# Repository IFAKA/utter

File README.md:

# Utter

**Live demo: https://utter-nine.vercel.app** · Goal: an open-source, non-invasive voice for people who cannot speak (for example ALS), measured in words per minute and word error rate on mimed speech.

Covert text input: silently articulate (lips closed, no sound) and text appears in any app.
Surface EMG (chin/throat/behind ear) -> Utter (2x ADS1298 = 16 ch + ESP32-S3) -> ~8 silent tokens -> local LLM suggestions -> earbud feedback -> typed text.

**Not a medical device.** Battery-powered operation only; the firmware refuses to record while USB is connected.

- docs/PLAN.md: stages and pass/fail gates
- docs/USAGE.md: setup and the user's 6 steps
- docs/HARDWARE.md, docs/ORDER.md: board design and order card
- Layout: hardware/ (generated KiCad board, `hardware/gen/build.sh`), firmware/ (PlatformIO), ml/ (`utter` host tools), app/ (Mac menu-bar app)

## Third-party data
- app/Sources/TypingCore/Resources/words_{en,es}.txt are derived from wordfreq (https://github.com/rspeer/wordfreq) word lists, CC-BY-SA 4.0. The derived lists keep that license.
- The Gaddy & Klein silent-speech EMG dataset (https://zenodo.org/records/4064409), CC-BY-4.0, is downloaded locally and not redistributed.

## Status
Early research. The board is designed (DRC/ERC clean) but not built or ordered. Nothing here is validated on people yet; see docs/PLAN.md for the pass/fail gates.

## License
No license chosen yet. Word lists keep CC-BY-SA 4.0 (see above).

---

## Support

If this project is useful to you, you can support my work:

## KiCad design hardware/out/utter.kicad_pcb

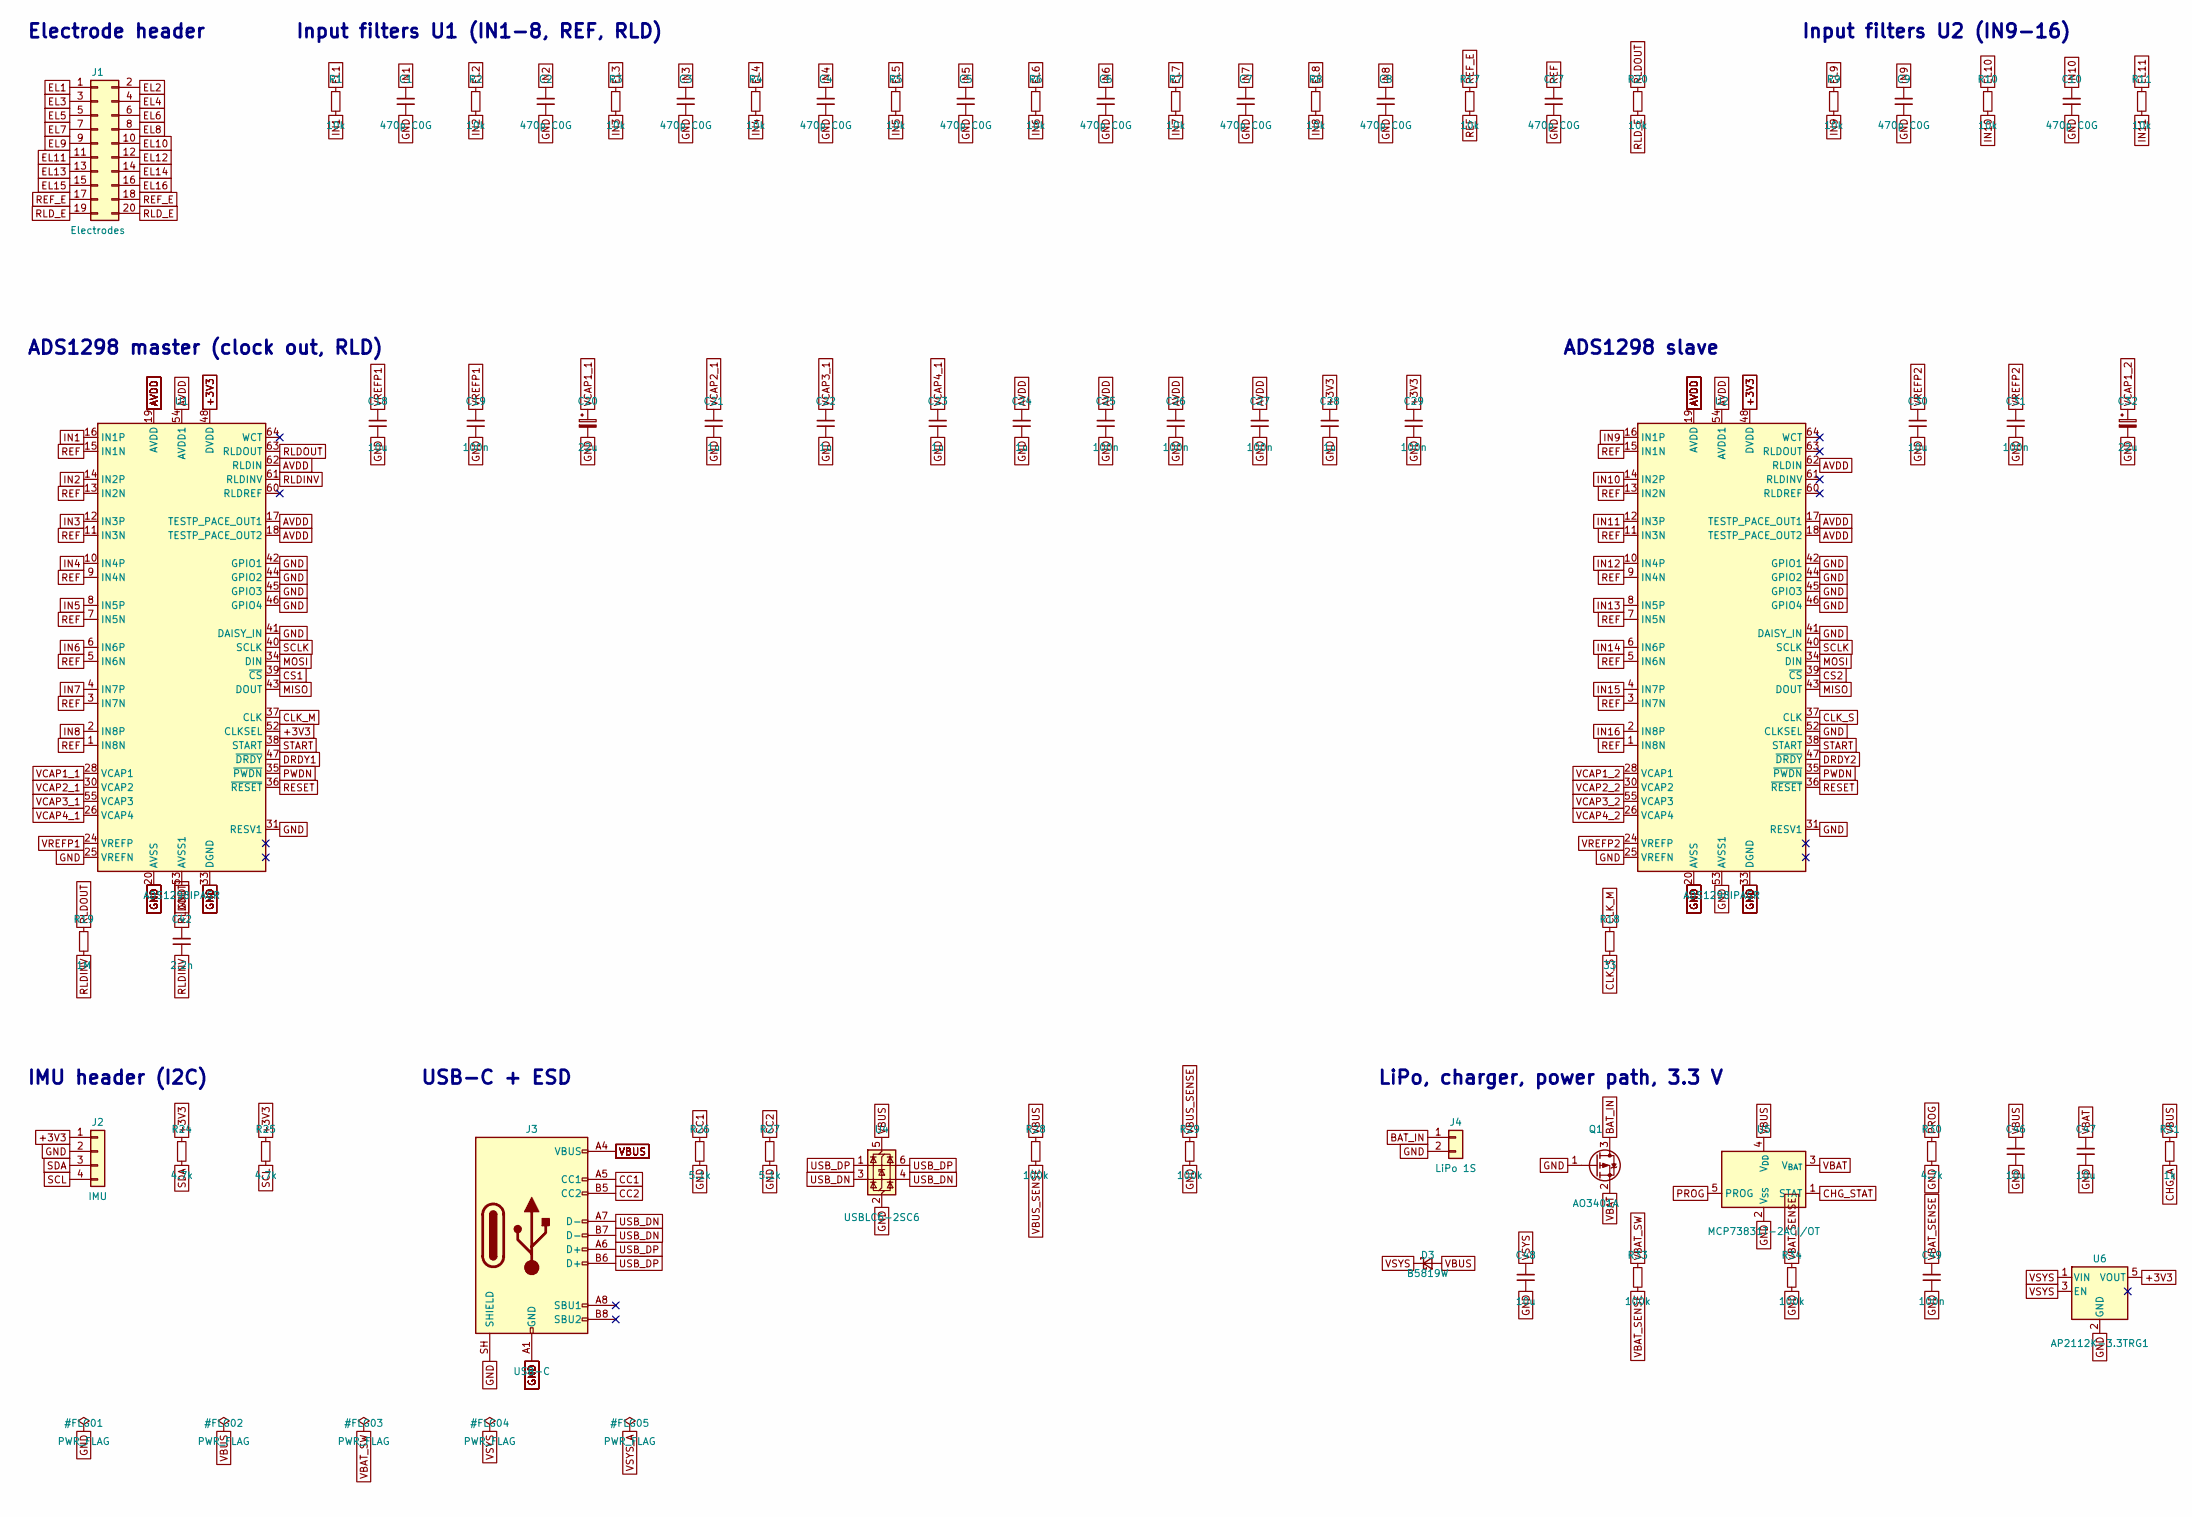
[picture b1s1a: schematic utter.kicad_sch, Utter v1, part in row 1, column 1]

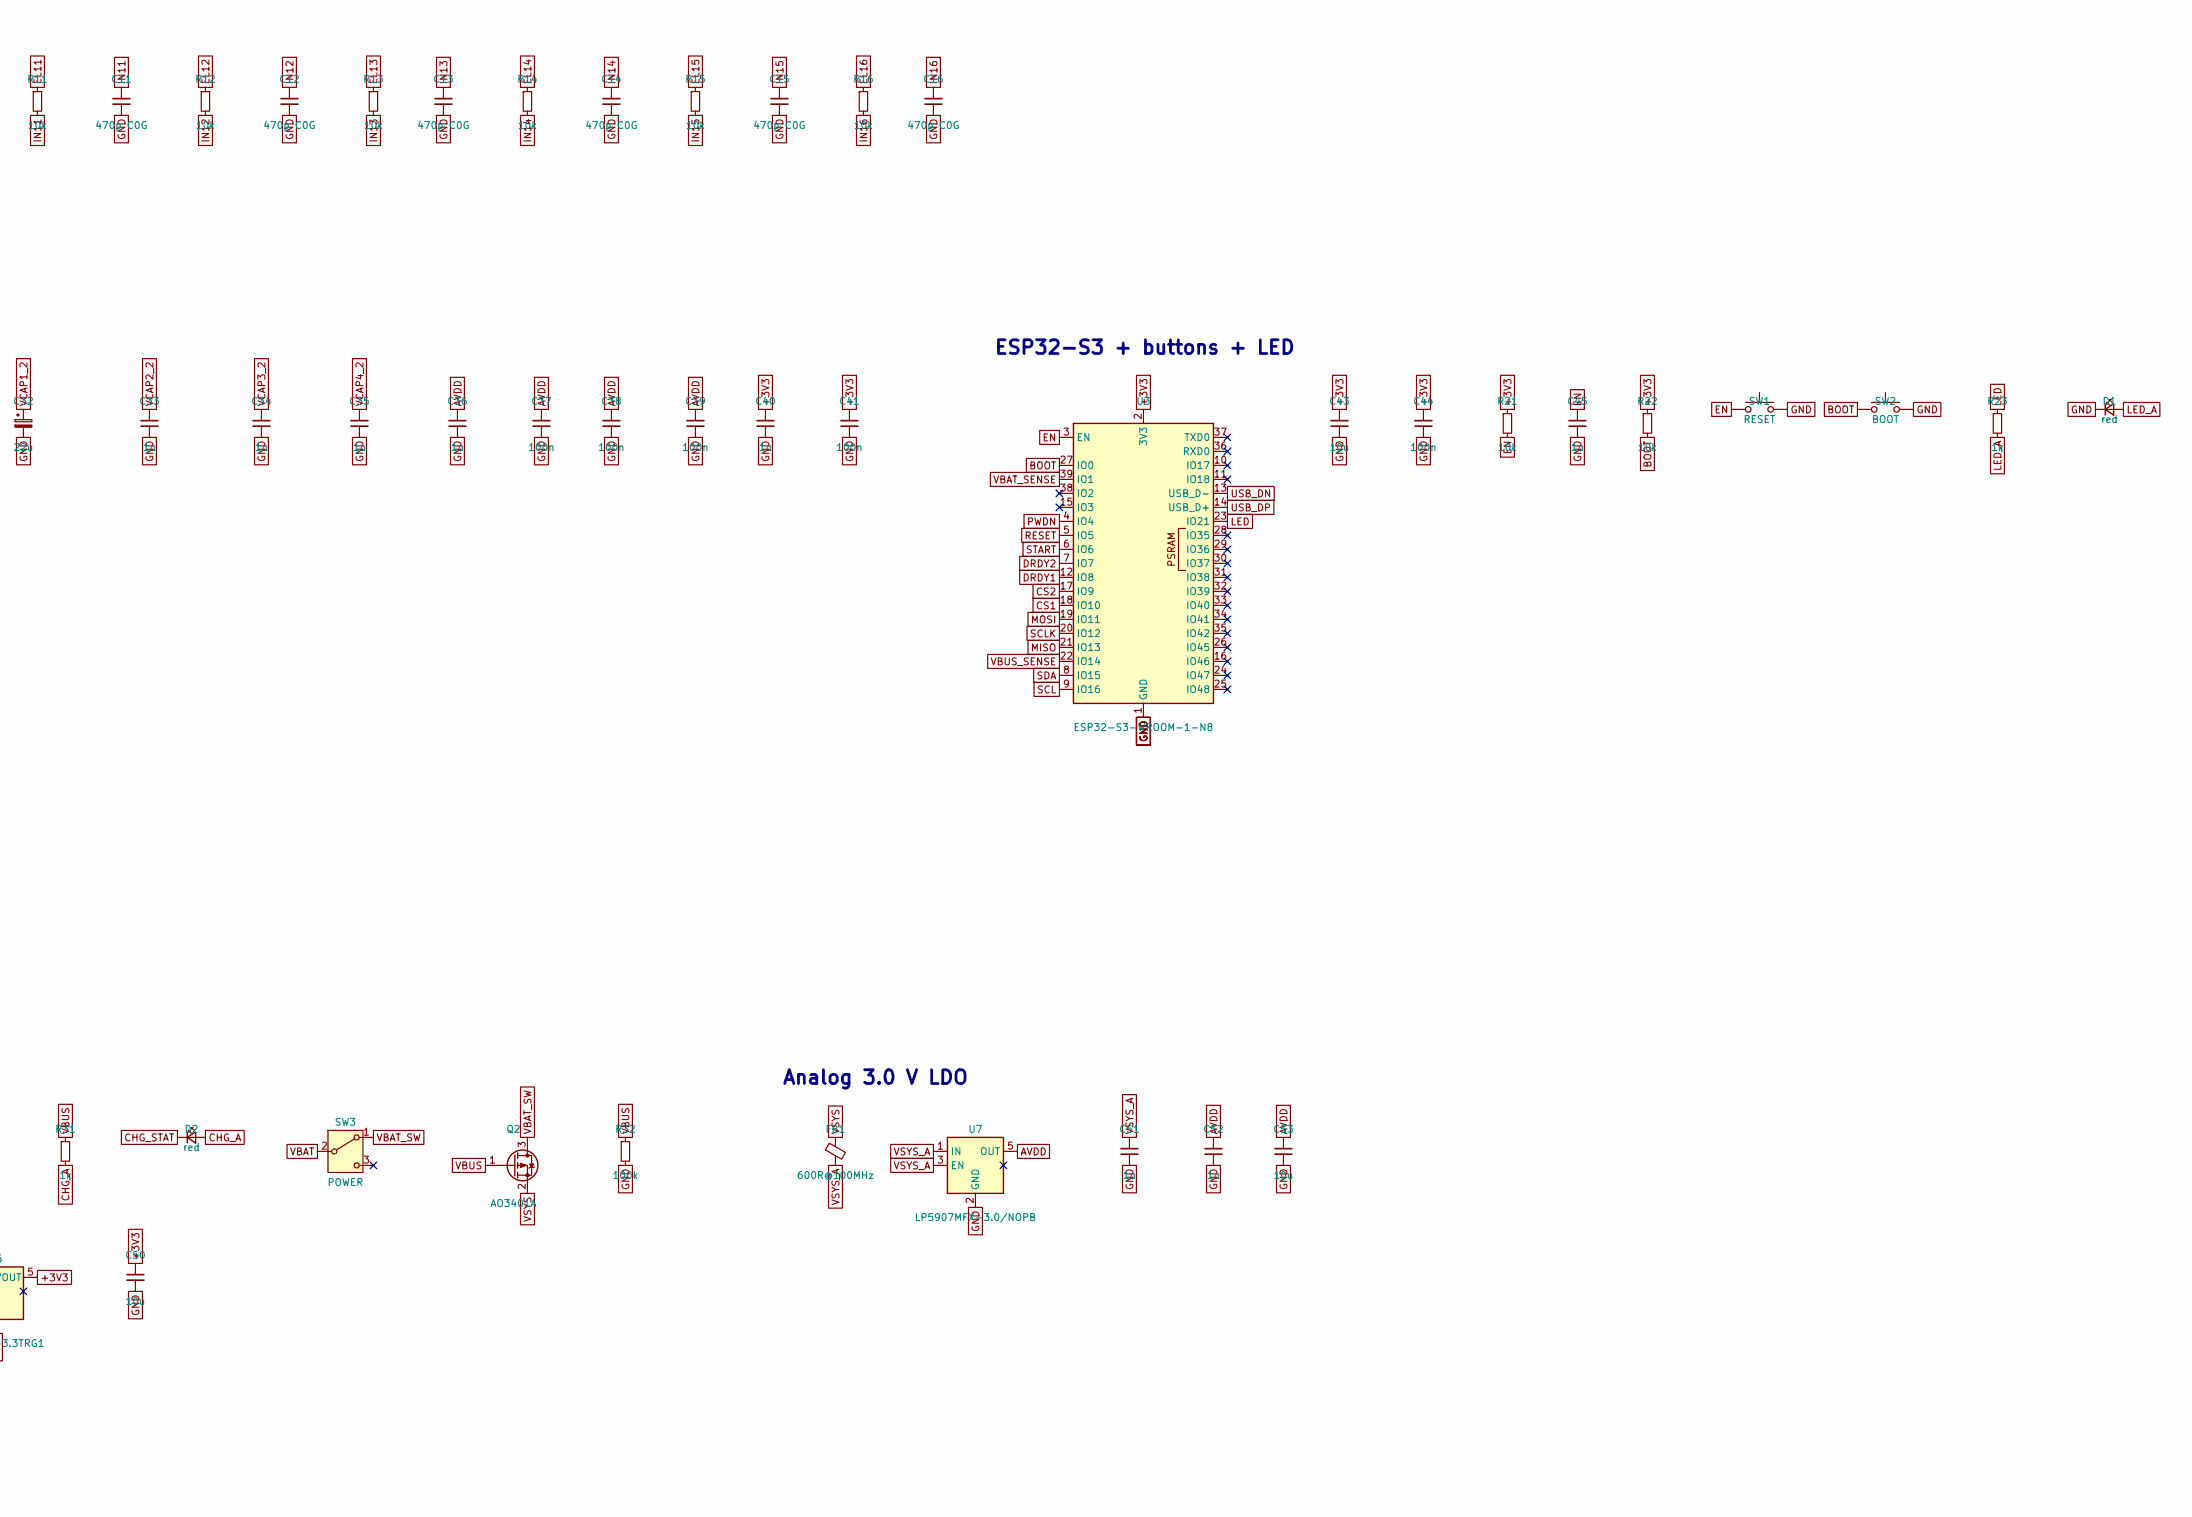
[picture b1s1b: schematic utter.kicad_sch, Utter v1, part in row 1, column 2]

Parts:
C1, C2, C3, C4, C5, C6, C7, C8, C9, C10, C11, C12, C13, C14, C15, C16, C17: 470p C0G; C_0402_1005Metric; LCSC C75274
C18, C30, C43, C46, C47, C48, C50, C53: 10u; C_0603_1608Metric; LCSC C19702
C19, C25, C26, C27, C29, C31, C37, C38, C39, C41, C44, C49: 100n; C_0402_1005Metric; LCSC C1525
C20, C32: 22u; CP_EIA-3216-18_Kemet-A; LCSC C7183
C21, C22, C23, C24, C28, C33, C34, C35, C36, C40, C45, C51, C52: 1u; C_0603_1608Metric; LCSC C15849
C42: 2.2n; C_0603_1608Metric; LCSC C1604
D1, D2: red; LED_0603_1608Metric; LCSC C2286
D3: B5819W; D_SOD-123; LCSC C8598
FB1: 600R@100MHz; L_0603_1608Metric; LCSC C1002
J1: Electrodes; PinHeader_2x10_P2.54mm_Vertical_SMD; LCSC C42372532
J2: IMU; PinHeader_1x04_P2.54mm_Vertical_SMD_Pin1Left; LCSC C46061677
J3: USB-C; USB_C_Receptacle_HRO_TYPE-C-31-M-12; LCSC C165948
J4: LiPo 1S; JST_PH_S2B-PH-SM4-TB_1x02-1MP_P2.00mm_Horizontal; LCSC C295747
Q1, Q2: AO3401A; SOT-23; LCSC C15127
R1, R2, R3, R4, R5, R6, R7, R8, R9, R10, R11, R12, R13, R14, R15, R16, R17, R20, R21, R22: 10k; R_0402_1005Metric; LCSC C25744
R18: 33; R_0402_1005Metric; LCSC C25105
R19: 1M; R_0402_1005Metric; LCSC C26083
R23, R31: 1k; R_0402_1005Metric; LCSC C11702
R24, R25, R30: 4.7k; R_0402_1005Metric; LCSC C25900
R26, R27: 5.1k; R_0402_1005Metric; LCSC C25905
R28, R29, R32, R33, R34: 100k; R_0402_1005Metric; LCSC C25741
SW1: RESET; SW_Push_1P1T_XKB_TS-1187A; LCSC C318884
SW2: BOOT; SW_Push_1P1T_XKB_TS-1187A; LCSC C318884
SW3: POWER; SW_SPDT_Shouhan_MSK12C02; LCSC C431540
U1, U2: ADS1298IPAGR; TQFP-64_10x10mm_P0.5mm; LCSC C527440
U3: ESP32-S3-WROOM-1-N8; ESP32-S3-WROOM-1; LCSC C2913198
U4: USBLC6-2SC6; SOT-23-6; LCSC C7519
U5: MCP73831T-2ACI/OT; SOT-23-5; LCSC C424093
U6: AP2112K-3.3TRG1; SOT-23-5; LCSC C51118
U7: LP5907MFX-3.0/NOPB; SOT-23-5; LCSC C475492

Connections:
+3V3: C28.1, C29.1, C40.1, C41.1, C43.1, C44.1, C50.1, J2.1, R21.1, R22.1, R24.1, R25.1, U1.48 (DVDD), U1.50 (DVDD), U1.52 (CLKSEL), U2.48 (DVDD), U2.50 (DVDD), U3.2 (3V3), U6.5 (VOUT)
AVDD: C24.1, C25.1, C26.1, C27.1, C36.1, C37.1, C38.1, C39.1, C52.1, C53.1, U1.17 (TESTP_PACE_OUT1), U1.18 (TESTP_PACE_OUT2), U1.19 (AVDD), U1.21 (AVDD), U1.22 (AVDD), U1.54 (AVDD1), U1.56 (AVDD), U1.59 (AVDD), U1.62 (RLDIN), U2.17 (TESTP_PACE_OUT1), U2.18 (TESTP_PACE_OUT2), U2.19 (AVDD), U2.21 (AVDD), U2.22 (AVDD), U2.54 (AVDD1), U2.56 (AVDD), U2.59 (AVDD), U2.62 (RLDIN), U7.5 (OUT)
BAT_IN: J4.1, Q1.3 (D)
BOOT: R22.2, SW2.1, U3.27 (IO0)
CC1: J3.A5 (CC1), R26.1
CC2: J3.B5 (CC2), R27.1
CHG_A: D2.2 (A), R31.2
CHG_STAT: D2.1 (K), U5.1 (STAT)
CLK_M: R18.1, U1.37 (CLK)
CLK_S: R18.2, U2.37 (CLK)
CS1: U1.39 (~CS), U3.18 (IO10)
CS2: U2.39 (~CS), U3.17 (IO9)
DRDY1: U1.47 (~DRDY), U3.12 (IO8)
DRDY2: U2.47 (~DRDY), U3.7 (IO7)
EL1: J1.1, R1.1
EL2: J1.2, R2.1
EL3: J1.3, R3.1
EL4: J1.4, R4.1
EL5: J1.5, R5.1
EL6: J1.6, R6.1
EL7: J1.7, R7.1
EL8: J1.8, R8.1
EL9: J1.9, R9.1
EL10: J1.10, R10.1
EL11: J1.11, R11.1
EL12: J1.12, R12.1
EL13: J1.13, R13.1
EL14: J1.14, R14.1
EL15: J1.15, R15.1
EL16: J1.16, R16.1
EN: C45.1, R21.2, SW1.1, U3.3 (EN)
GND: C1.2, C2.2, C3.2, C4.2, C5.2, C6.2, C7.2, C8.2, C9.2, C10.2, C11.2, C12.2, C13.2, C14.2, C15.2, C16.2, C17.2, C18.2, C19.2, C20.2, C21.2, C22.2, C23.2, C24.2, C25.2, C26.2, C27.2, C28.2, C29.2, C30.2, C31.2, C32.2, C33.2, C34.2, C35.2, C36.2, C37.2, C38.2, C39.2, C40.2, C41.2, C43.2, C44.2, C45.2, C46.2, C47.2, C48.2, C49.2, C50.2, C51.2, C52.2, C53.2, D1.1 (K), J2.2, J3.A1 (GND), J3.A12 (GND), J3.B1 (GND), J3.B12 (GND), J3.SH (SHIELD), J4.2, J4.MP, Q1.1 (G), R26.2, R27.2, R29.2, R30.2, R32.2, R34.2, SW1.2, SW2.2, SW3.SH, U1.20 (AVSS), U1.23 (AVSS), U1.25 (VREFN), U1.31 (RESV1), U1.32 (AVSS), U1.33 (DGND), U1.41 (DAISY_IN), U1.42 (GPIO1), U1.44 (GPIO2), U1.45 (GPIO3), U1.46 (GPIO4), U1.49 (DGND), U1.51 (DGND), U1.53 (AVSS1), U1.57 (AVSS), U1.58 (AVSS), U2.20 (AVSS), U2.23 (AVSS), U2.25 (VREFN), U2.31 (RESV1), U2.32 (AVSS), U2.33 (DGND), U2.41 (DAISY_IN), U2.42 (GPIO1), U2.44 (GPIO2), U2.45 (GPIO3), U2.46 (GPIO4), U2.49 (DGND), U2.51 (DGND), U2.52 (CLKSEL), U2.53 (AVSS1), U2.57 (AVSS), U2.58 (AVSS), U3.1 (GND), U3.40 (GND), U3.41 (GND), U4.2 (GND), U5.2 (V_{SS}), U6.2 (GND), U7.2 (GND)
IN1: C1.1, R1.2, U1.16 (IN1P)
IN2: C2.1, R2.2, U1.14 (IN2P)
IN3: C3.1, R3.2, U1.12 (IN3P)
IN4: C4.1, R4.2, U1.10 (IN4P)
IN5: C5.1, R5.2, U1.8 (IN5P)
IN6: C6.1, R6.2, U1.6 (IN6P)
IN7: C7.1, R7.2, U1.4 (IN7P)
IN8: C8.1, R8.2, U1.2 (IN8P)
IN9: C9.1, R9.2, U2.16 (IN1P)
IN10: C10.1, R10.2, U2.14 (IN2P)
IN11: C11.1, R11.2, U2.12 (IN3P)
IN12: C12.1, R12.2, U2.10 (IN4P)
IN13: C13.1, R13.2, U2.8 (IN5P)
IN14: C14.1, R14.2, U2.6 (IN6P)
IN15: C15.1, R15.2, U2.4 (IN7P)
IN16: C16.1, R16.2, U2.2 (IN8P)
LED: R23.1, U3.23 (IO21)
LED_A: D1.2 (A), R23.2
MISO: U1.43 (DOUT), U2.43 (DOUT), U3.21 (IO13)
MOSI: U1.34 (DIN), U2.34 (DIN), U3.19 (IO11)
NC_LDO1: U6.4 (NC)
NC_LDO2: U7.4 (NC)
NC_SW: SW3.3 (C)
PROG: R30.1, U5.5 (PROG)
PWDN: U1.35 (~PWDN), U2.35 (~PWDN), U3.4 (IO4)
REF: C17.1, R17.2, U1.1 (IN8N), U1.3 (IN7N), U1.5 (IN6N), U1.7 (IN5N), U1.9 (IN4N), U1.11 (IN3N), U1.13 (IN2N), U1.15 (IN1N), U2.1 (IN8N), U2.3 (IN7N), U2.5 (IN6N), U2.7 (IN5N), U2.9 (IN4N), U2.11 (IN3N), U2.13 (IN2N), U2.15 (IN1N)
REF_E: J1.17, J1.18, R17.1
RESET: U1.36 (~RESET), U2.36 (~RESET), U3.5 (IO5)
RLDINV: C42.2, R19.2, U1.61 (RLDINV)
RLDOUT: C42.1, R19.1, R20.1, U1.63 (RLDOUT)
RLD_E: J1.19, J1.20, R20.2
SCL: J2.4, R25.2, U3.9 (IO16)
SCLK: U1.40 (SCLK), U2.40 (SCLK), U3.20 (IO12)
SDA: J2.3, R24.2, U3.8 (IO15)
START: U1.38 (START), U2.38 (START), U3.6 (IO6)
USB_DN: J3.A7 (D-), J3.B7 (D-), U3.13 (USB_D-), U4.3 (I/O2), U4.4 (I/O2)
USB_DP: J3.A6 (D+), J3.B6 (D+), U3.14 (USB_D+), U4.1 (I/O1), U4.6 (I/O1)
VBAT: C47.1, Q1.2 (S), SW3.2 (B), U5.3 (V_{BAT})
VBAT_SENSE: C49.1, R33.2, R34.1, U3.39 (IO1)
VBAT_SW: Q2.3 (D), R33.1, SW3.1 (A)
VBUS: C46.1, D3.2 (A), J3.A4 (VBUS), J3.A9 (VBUS), J3.B4 (VBUS), J3.B9 (VBUS), Q2.1 (G), R28.1, R31.1, R32.1, U4.5 (VBUS), U5.4 (V_{DD})
VBUS_SENSE: R28.2, R29.1, U3.22 (IO14)
VCAP1_1: C20.1, U1.28 (VCAP1)
VCAP1_2: C32.1, U2.28 (VCAP1)
VCAP2_1: C21.1, U1.30 (VCAP2)
VCAP2_2: C33.1, U2.30 (VCAP2)
VCAP3_1: C22.1, U1.55 (VCAP3)
VCAP3_2: C34.1, U2.55 (VCAP3)
VCAP4_1: C23.1, U1.26 (VCAP4)
VCAP4_2: C35.1, U2.26 (VCAP4)
VREFP1: C18.1, C19.1, U1.24 (VREFP)
VREFP2: C30.1, C31.1, U2.24 (VREFP)
VSYS: C48.1, D3.1 (K), FB1.1, Q2.2 (S), U6.1 (VIN), U6.3 (EN)
VSYS_A: C51.1, FB1.2, U7.1 (IN), U7.3 (EN)

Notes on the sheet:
Electrode header
Input filters U1 (IN1-8, REF, RLD)
Input filters U2 (IN9-16)
ADS1298 master (clock out, RLD)
ADS1298 slave
ESP32-S3 + buttons + LED
IMU header (I2C)
USB-C + ESD
LiPo, charger, power path, 3.3 V
Analog 3.0 V LDO

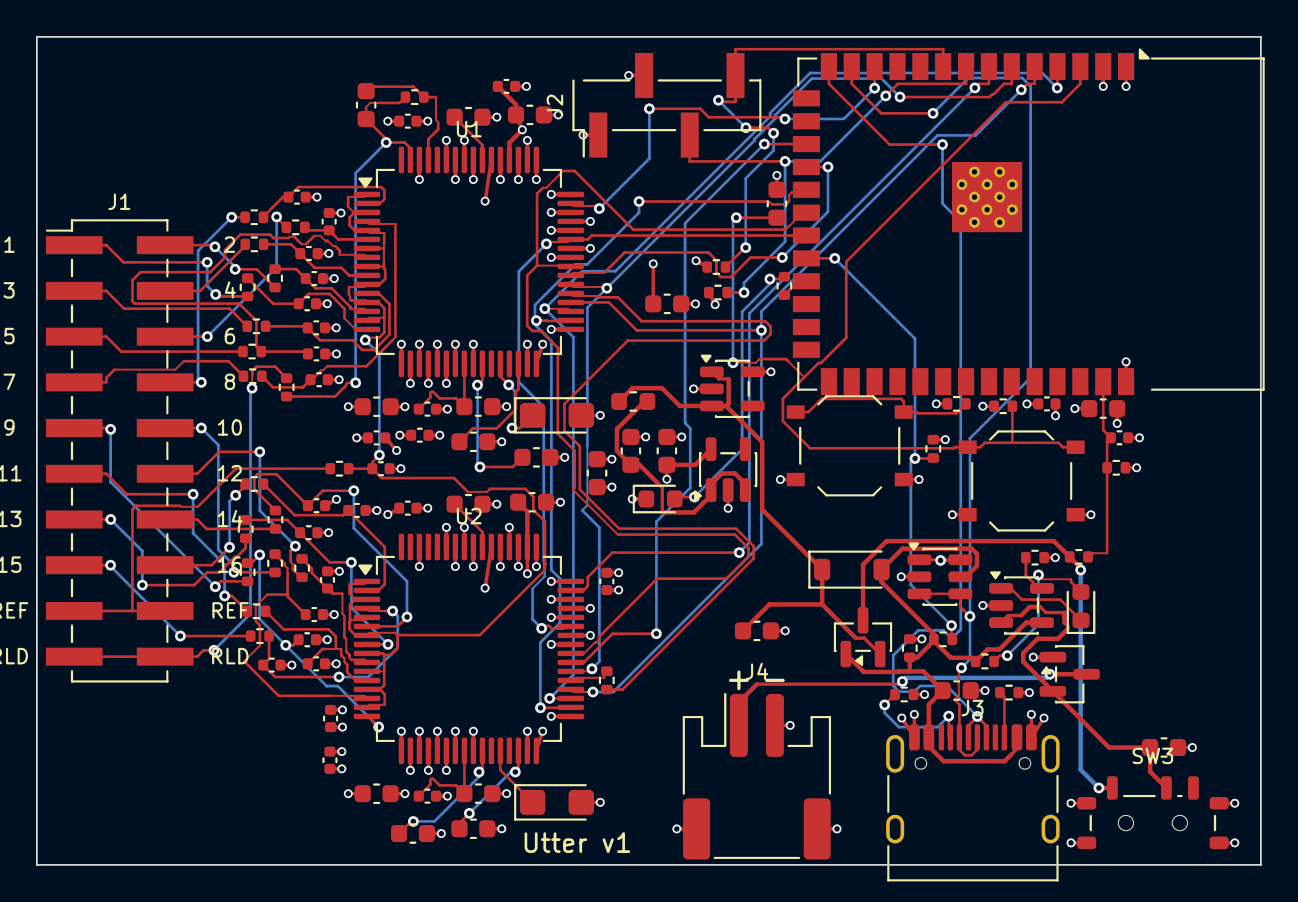
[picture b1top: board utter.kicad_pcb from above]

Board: 4 copper layers, 68.0 x 46.0 mm, 107 parts (0 on the bottom side), 83 nets.

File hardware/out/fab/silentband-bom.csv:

Comment,Designator,Footprint,LCSC Part #,Quantity
470p C0G,"C1,C2,C3,C4,C5,C6,C7,C8,C9,C10,C11,C12,C13,C14,C15,C16,C17",C_0402_1005Metric,C75274,17
10u,"C18,C30,C43,C46,C47,C48,C50,C53",C_0603_1608Metric,C19702,8
100n,"C19,C25,C26,C27,C29,C31,C37,C38,C39,C41,C44,C49",C_0402_1005Metric,C1525,12
22u,"C20,C32",CP_EIA-3216-18_Kemet-A,C7183,2
1u,"C21,C22,C23,C24,C28,C33,C34,C35,C36,C40,C45,C51,C52",C_0603_1608Metric,C15849,13
2.2n,C42,C_0603_1608Metric,C1604,1
red,"D1,D2",LED_0603_1608Metric,C2286,2
B5819W,D3,D_SOD-123,C8598,1
600R@100MHz,FB1,L_0603_1608Metric,C1002,1
Electrodes,J1,PinHeader_2x10_P2.54mm_Vertical_SMD,C42372532,1
IMU,J2,PinHeader_1x04_P2.54mm_Vertical_SMD_Pin1Left,C46061677,1
USB-C,J3,USB_C_Receptacle_HRO_TYPE-C-31-M-12,C165948,1
LiPo 1S,J4,JST_PH_S2B-PH-SM4-TB_1x02-1MP_P2.00mm_Horizontal,C295747,1
AO3401A,"Q1,Q2",SOT-23,C15127,2
10k,"R1,R2,R3,R4,R5,R6,R7,R8,R9,R10,R11,R12,R13,R14,R15,R16,R17,R20,R21,R22",R_0402_1005Metric,C25744,20
33,R18,R_0402_1005Metric,C25105,1
1M,R19,R_0402_1005Metric,C26083,1
1k,"R23,R31",R_0402_1005Metric,C11702,2
4.7k,"R24,R25,R30",R_0402_1005Metric,C25900,3
5.1k,"R26,R27",R_0402_1005Metric,C25905,2
100k,"R28,R29,R32,R33,R34",R_0402_1005Metric,C25741,5
RESET,SW1,SW_Push_1P1T_XKB_TS-1187A,C318884,1
BOOT,SW2,SW_Push_1P1T_XKB_TS-1187A,C318884,1
POWER,SW3,SW_SPDT_Shouhan_MSK12C02,C431540,1
ADS1298IPAGR,"U1,U2",TQFP-64_10x10mm_P0.5mm,C527440,2
ESP32-S3-WROOM-1-N8,U3,ESP32-S3-WROOM-1,C2913198,1
USBLC6-2SC6,U4,SOT-23-6,C7519,1
MCP73831T-2ACI/OT,U5,SOT-23-5,C424093,1
AP2112K-3.3TRG1,U6,SOT-23-5,C51118,1
LP5907MFX-3.0/NOPB,U7,SOT-23-5,C475492,1

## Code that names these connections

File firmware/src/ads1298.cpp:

#include "ads1298.h"
#include "pins.h"
#include <driver/gpio.h>

namespace ads {
static SPIClass spi(FSPI);
static const SPISettings cfg(8000000, MSBFIRST, SPI_MODE1);
static const int cs[NCHIP] = {PIN_CS1, PIN_CS2};
// fCLK = 2.048 MHz: multi-byte commands need 4 tCLK (~2 us) between bytes.
static inline void tdecode() { delayMicroseconds(3); }

enum Op : uint8_t { WAKEUP = 0x02, RESET = 0x06, RDATAC = 0x10, SDATAC = 0x11, RREG = 0x20, WREG = 0x40 };

static void op(int chip, uint8_t c) {
  spi.beginTransaction(cfg);
  digitalWrite(cs[chip], LOW);
  spi.transfer(c);
  tdecode();
  digitalWrite(cs[chip], HIGH);
  spi.endTransaction();
}

uint8_t readReg(int chip, uint8_t reg) {
  spi.beginTransaction(cfg);
  digitalWrite(cs[chip], LOW);
  spi.transfer(RREG | reg); tdecode();
  spi.transfer(0); tdecode();
  uint8_t v = spi.transfer(0); tdecode();
  digitalWrite(cs[chip], HIGH);
  spi.endTransaction();
  return v;
}

void writeReg(int chip, uint8_t reg, uint8_t val) {
  spi.beginTransaction(cfg);
  digitalWrite(cs[chip], LOW);
  spi.transfer(WREG | reg); tdecode();
  spi.transfer(0); tdecode();
  spi.transfer(val); tdecode();
  digitalWrite(cs[chip], HIGH);
  spi.endTransaction();
}

// HR-mode DR codes; CONFIG1 = HR | DAISY_EN (multiple readback) | CLK_EN (master only) | DR.
static int drCode(int fs) {
  switch (fs) {
    case 500: return 6; case 1000: return 5; case 2000: return 4; case 4000: return 3;
    default: return -1;
  }
}
static int gainCode(int g) {
  switch (g) {
    case 6: return 0; case 1: return 1; case 2: return 2; case 3: return 3;
    case 4: return 4; case 8: return 5; case 12: return 6; default: return -1;
  }
}

void begin() {
  for (int c : cs) { pinMode(c, OUTPUT); digitalWrite(c, HIGH); }
  pinMode(PIN_START, OUTPUT); digitalWrite(PIN_START, LOW);
  pinMode(PIN_RESET, OUTPUT); digitalWrite(PIN_RESET, HIGH);
  pinMode(PIN_PWDN, OUTPUT); digitalWrite(PIN_PWDN, HIGH);
  pinMode(PIN_DRDY1, INPUT_PULLUP);
  pinMode(PIN_DRDY2, INPUT_PULLUP);
  spi.begin(PIN_SCLK, PIN_MISO, PIN_MOSI, -1);
  // weakest drive = slowest edges: SPI/control lines partly run on B.Cu over the analog half
  for (int p : {PIN_SCLK, PIN_MOSI, PIN_CS1, PIN_CS2, PIN_START, PIN_RESET, PIN_PWDN})
    gpio_set_drive_capability((gpio_num_t)p, GPIO_DRIVE_CAP_0);
  delay(200);                                   // power-on reset: 2^18 tCLK = 128 ms
  digitalWrite(PIN_RESET, LOW); delayMicroseconds(10); digitalWrite(PIN_RESET, HIGH);
  delayMicroseconds(20);                        // 18 tCLK
  op(0, SDATAC);
  writeReg(0, CONFIG1, 0xE4);                   // master: CLK_EN so the slave gets a clock
  delay(150);                                   // slave tPOR (128 ms) starts only once CLK is valid
  op(1, RESET);                                 // the slave now has a clock: reset it properly
  delayMicroseconds(20);
  op(1, SDATAC);
  for (int c = 0; c < NCHIP; c++) writeReg(c, CONFIG3, 0xC0);  // internal reference on
  delay(150);                                   // reference settling
}

bool configure(int fs, int gain, Mode mode, bool leadoff) {
  int dr = drCode(fs), g = gainCode(gain);
  if (dr < 0 || g < 0) return false;
  for (int c = 0; c < NCHIP; c++) {
    bool master = c == 0;
    writeReg(c, CONFIG1, 0x80 | 0x40 | (master ? 0x20 : 0) | dr);
    writeReg(c, CONFIG2, mode == TEST ? 0x10 : 0x00);         // internal test: 1 mV, fCLK/2^21
    // Refbuf on, RLDREF internal; only the master drives the right-leg (RLD) electrode.
    writeReg(c, CONFIG3, master ? 0xCC : 0xC8);
    writeReg(c, LOFF, 0x00);                                  // DC lead-off, 6 nA, 95% threshold
    for (int ch = 0; ch < 8; ch++) writeReg(c, CH1SET + ch, (g << 4) | mode);
    uint8_t rld = (master && mode == NORMAL) ? 0xFF : 0x00;
    writeReg(c, RLD_SENSP, rld);
    writeReg(c, RLD_SENSN, rld);
    uint8_t lo = (leadoff && mode == NORMAL) ? 0xFF : 0x00;
    writeReg(c, LOFF_SENSP, lo);
    writeReg(c, LOFF_SENSN, lo);
    writeReg(c, LOFF_FLIP, 0x00);
    writeReg(c, GPIO, 0x0F);                                  // GPIO1-4 inputs (tied to DGND on the board)
    writeReg(c, CONFIG4, lo ? 0x02 : 0x00);                   // lead-off comparators
    writeReg(c, WCT1, 0x00);
    writeReg(c, WCT2, 0x00);
  }
  return true;
}

void startStream() {
  for (int c = 0; c < NCHIP; c++) op(c, RDATAC);
  digitalWrite(PIN_START, HIGH);
}

void stopStream() {
  digitalWrite(PIN_START, LOW);
  for (int c = 0; c < NCHIP; c++) op(c, SDATAC);
}

void readFrame(uint8_t* out) {
  spi.beginTransaction(cfg);
  for (int c = 0; c < NCHIP; c++) {
    digitalWrite(cs[c], LOW);
    memset(out, 0, FRAME);
    spi.transferBytes(out, out, FRAME);  // DIN held low while reading
    digitalWrite(cs[c], HIGH);
    out += FRAME;
  }
  spi.endTransaction();
}
}  // namespace ads
